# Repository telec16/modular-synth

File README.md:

# Telec's Modular Synth

~~Little side project, don't expect much updates.~~

# List of stuff I want to make

| 0%   | 10% | 20%       | 50%    | 65%     | 70%           | 75%  | 80%   | 100% |
|----- |---- |---------- |------- |-------- |-------------- |----- |------ |----- |
| Idea | POC | Schematic | Layout | Artwork | Final checkup | Prod | Tests | Done |

## Modules

* VCO
	- 3340
	- Schmitt inverter
	- Opamp V1 
	- Opamp V2 
* LFO
	- Hex Inverter
* Sequencer
	- µC
	- random jazz generator 
* Random generator
	- zener
	- µC
* ADSR
	- Opamp 
* VCA
	- LM13700 
	- Vactrol
* Quantizer (CV correction)
	- µC 
* VCF
	- ?
* Drum kit
	- ???
* Frequency multiplier/divider
	- CD4046 PLL V1 
	- CD4046 PLL V2 
* Wavefolder
	- Bipolar 
	- Opamp 
* CV Glider
	- RC circuit 
* Scope
	- µC 

## Instruments

* MiniSynth 
* MIDI I/O + CV Out keypad 

# Releases

* ADSR
* CV Glider
* VCA
* Wavefolder
* VCO
* PLL

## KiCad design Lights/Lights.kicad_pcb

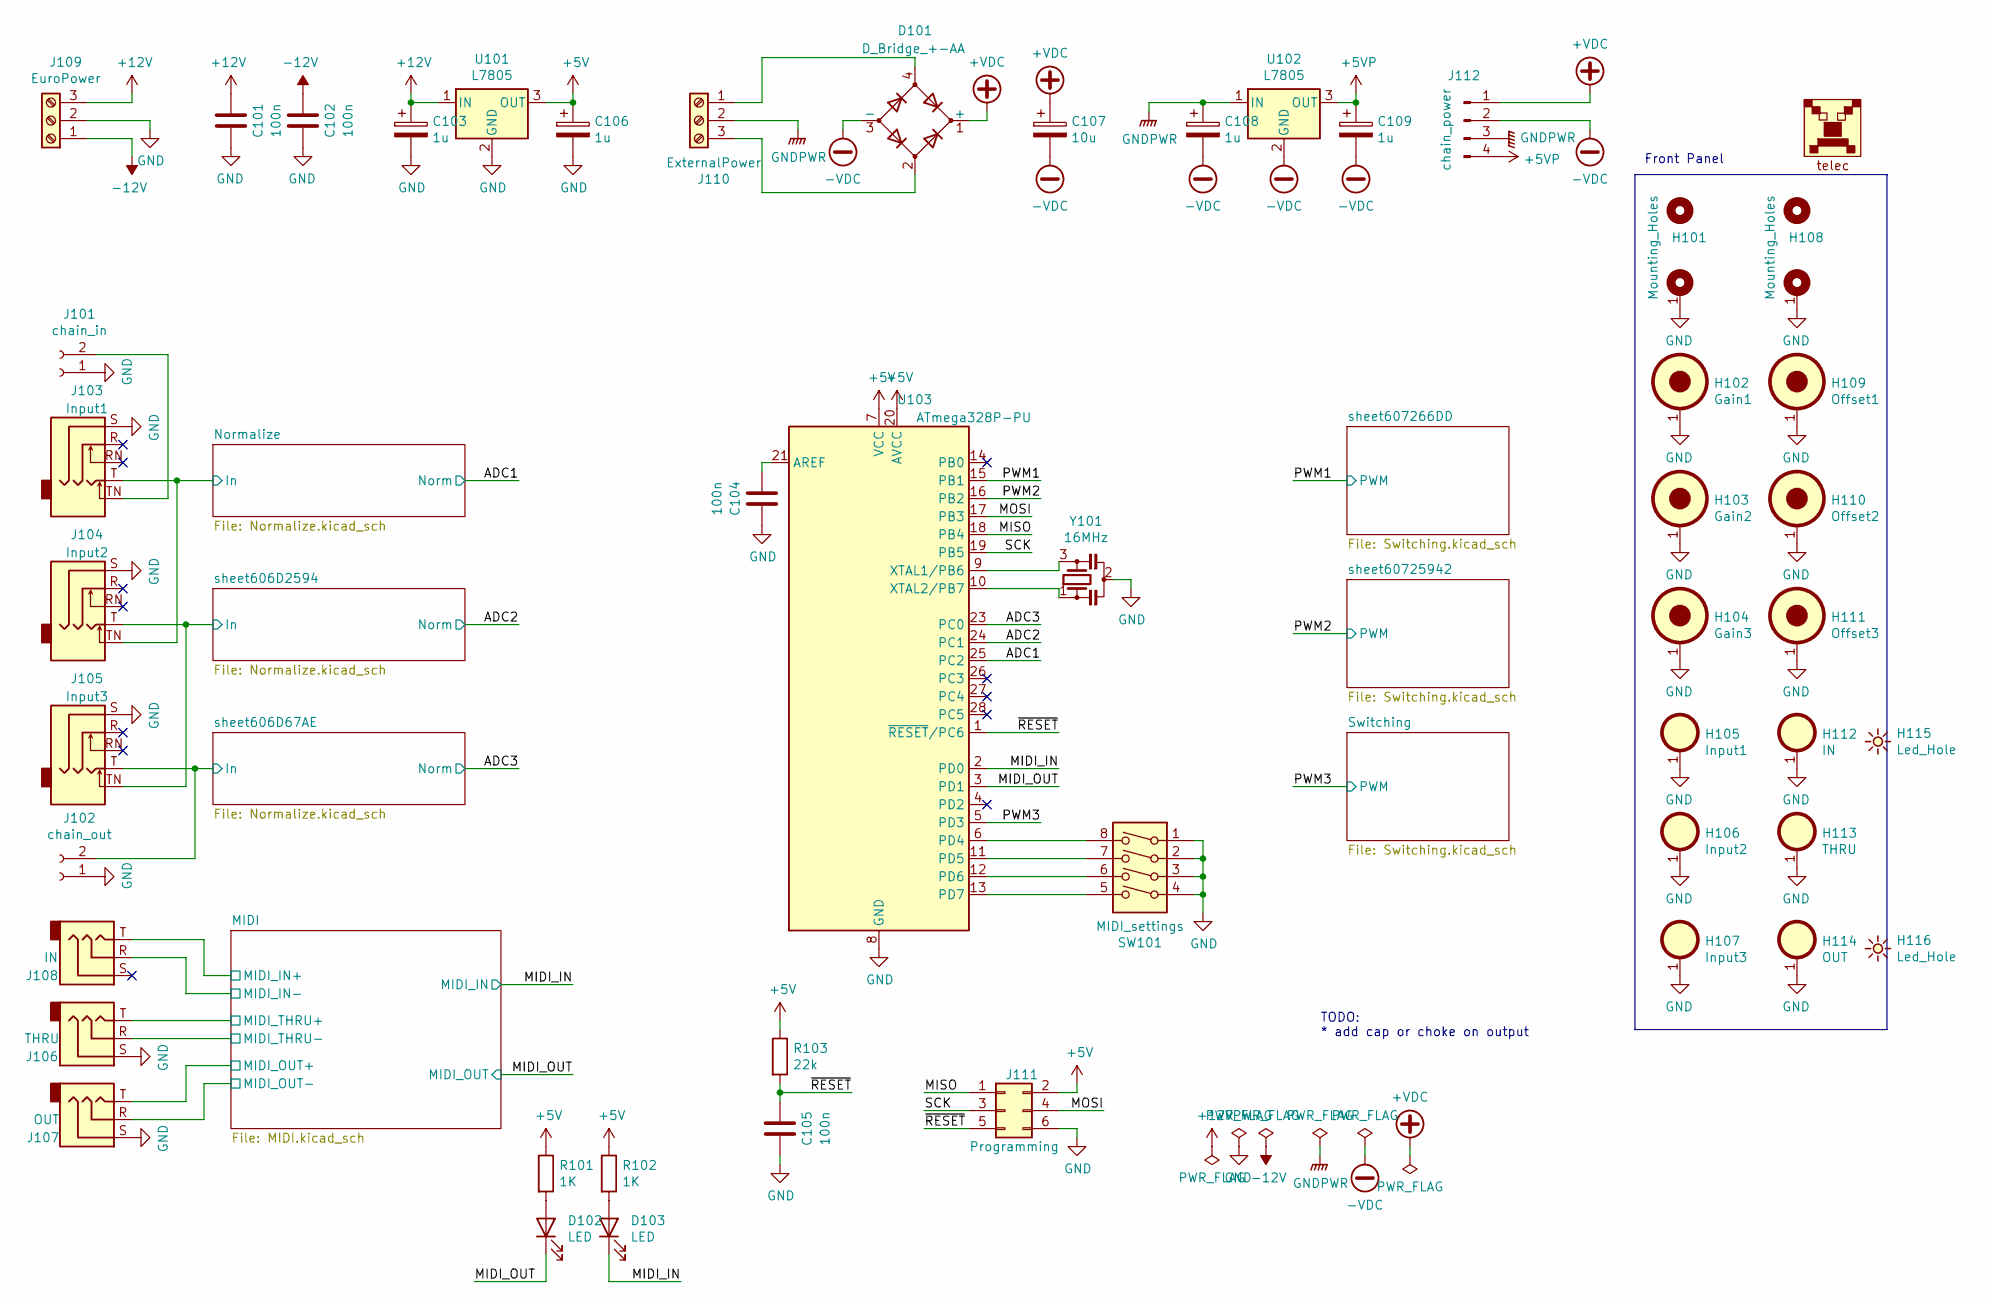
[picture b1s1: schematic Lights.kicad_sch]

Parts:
C101, C102, C104, C105: 100n; C_Disc_D7.0mm_W2.5mm_P5.00mm
C103, C106, C108, C109: 1u; CP_Radial_D5.0mm_P2.50mm
C107: 10u; CP_Radial_D5.0mm_P2.50mm
D101: D_Bridge_+-AA; Diode_Bridge_Round_D8.9mm
D102, D103: LED; LED_D3.0mm_FlatTop
H101, H108: Mounting_Holes; Kosmo_Panel_Dual_Mounting_Holes
H102: Gain1; Kosmo_Pot_Hole
H103: Gain2; Kosmo_Pot_Hole
H104: Gain3; Kosmo_Pot_Hole
H105: Input1; Kosmo_Jack_Hole
H106: Input2; Kosmo_Jack_Hole
H107: Input3; Kosmo_Jack_Hole
H109: Offset1; Kosmo_Pot_Hole
H110: Offset2; Kosmo_Pot_Hole
H111: Offset3; Kosmo_Pot_Hole
H112: IN; Kosmo_Jack_Hole
H113: THRU; Kosmo_Jack_Hole
H114: OUT; Kosmo_Jack_Hole
H115, H116: Led_Hole; Kosmo_LED_Hole
J101: chain_in; PinHeader_1x02_P2.54mm_Vertical
J102: chain_out; PinHeader_1x02_P2.54mm_Vertical
J103: Input1; Jack_6.35mm_PJ_629HAN
J104: Input2; Jack_6.35mm_PJ_629HAN
J105: Input3; Jack_6.35mm_PJ_629HAN
J106: THRU; PinHeader_TRS_P2.54mm_Vertical
J107: OUT; PinHeader_TRS_P2.54mm_Vertical
J108: IN; PinHeader_TRS_P2.54mm_Vertical
J109: EuroPower
J110: ExternalPower; TerminalBlock_bornier-3_P5.08mm
J111: Programming; IDC-Header_2x03_P2.54mm_Vertical
J112: chain_power; PinHeader_1x04_P2.54mm_Vertical
LOGO101: telec; telec-8
R101, R102: 1K; R_Axial_DIN0204_L3.6mm_D1.6mm_P2.54mm_Vertical
R103: 22k; R_Axial_DIN0204_L3.6mm_D1.6mm_P2.54mm_Vertical
SW101: MIDI_settings; SW_DIP_SPSTx04_Slide_9.78x12.34mm_W7.62mm_P2.54mm
U101, U102: L7805; TO-220-3_Vertical
U103: ATmega328P-PU; DIP-28_W7.62mm
Y101: 16MHz; Resonator-3Pin_W6.0mm_H3.0mm

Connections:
+5V: C106.1, J111.2, R101.1, R102.1, R103.1, U101.3 (OUT), U103.7 (VCC), U103.20 (AVCC); also elsewhere on the board
+5VP: C109.1, J112.4, U102.3 (OUT); also elsewhere on the board
+12V: C101.2, C103.1, J109.3, U101.1 (IN); also elsewhere on the board
+VDC: C107.1, D101.1 (+), J112.1; also elsewhere on the board
-12V: C102.2, J109.1; also elsewhere on the board
-VDC: C107.2, C108.2, C109.2, D101.3 (-), J112.2, U102.2 (GND); also elsewhere on the board
/ADC1: U103.25 (PC2); also elsewhere on the board
/ADC2: U103.24 (PC1); also elsewhere on the board
/ADC3: U103.23 (PC0); also elsewhere on the board
/MIDI/MIDI_IN+: J108.T; also elsewhere on the board
/MIDI/MIDI_IN-: J108.R; also elsewhere on the board
/MIDI/MIDI_OUT+: J107.T; also elsewhere on the board
/MIDI/MIDI_OUT-: J107.R; also elsewhere on the board
/MIDI/MIDI_THRU+: J106.T; also elsewhere on the board
/MIDI/MIDI_THRU-: J106.R; also elsewhere on the board
/MIDI_IN: D103.1 (K), U103.2 (PD0); also elsewhere on the board
/MIDI_OUT: D102.1 (K), U103.3 (PD1); also elsewhere on the board
/MISO: J111.1, U103.18 (PB4)
/MOSI: J111.4, U103.17 (PB3)
/Normalize/In: J103.T, J104.TN; also elsewhere on the board
/PWM1: U103.15 (PB1); also elsewhere on the board
/PWM2: U103.16 (PB2); also elsewhere on the board
/PWM3: U103.5 (PD3); also elsewhere on the board
/SCK: J111.3, U103.19 (PB5)
/sheet606D67AE/In: J102.2, J105.T; also elsewhere on the board
/sheet606D2594/In: J104.T, J105.TN; also elsewhere on the board
/~RESET: C105.2, J111.5, R103.2, U103.1 (~RESET/PC6)
GND: C101.1, C102.1, C103.2, C104.1, C105.1, C106.2, H101.1, H102.1, H103.1, H104.1, H105.1, H106.1, H107.1, H108.1, H109.1, H110.1, H111.1, H112.1, H113.1, H114.1, J101.1, J102.1, J103.S, J104.S, J105.S, J106.S, J107.S, J109.2, J111.6, SW101.1, SW101.2, SW101.3, SW101.4, U101.2 (GND), U103.8 (GND), U103.22 (GND), Y101.2; also elsewhere on the board
GNDPWR: C108.1, J110.2, J112.3, U102.1 (IN)
unnamed: D102.2 (A), R101.2
unnamed: D103.2 (A), R102.2
unnamed: J101.2, J103.TN
unnamed: D101.4, J110.1
unnamed: D101.2, J110.3
unnamed: C104.2, U103.21 (AREF)
unnamed: SW101.8, U103.6 (PD4)
unnamed: SW101.7, U103.11 (PD5)
unnamed: SW101.6, U103.12 (PD6)
unnamed: SW101.5, U103.13 (PD7)
unnamed: U103.9 (XTAL1/PB6), Y101.3
unnamed: U103.10 (XTAL2/PB7), Y101.1

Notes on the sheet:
TODO: * add cap or choke on output
Front Panel

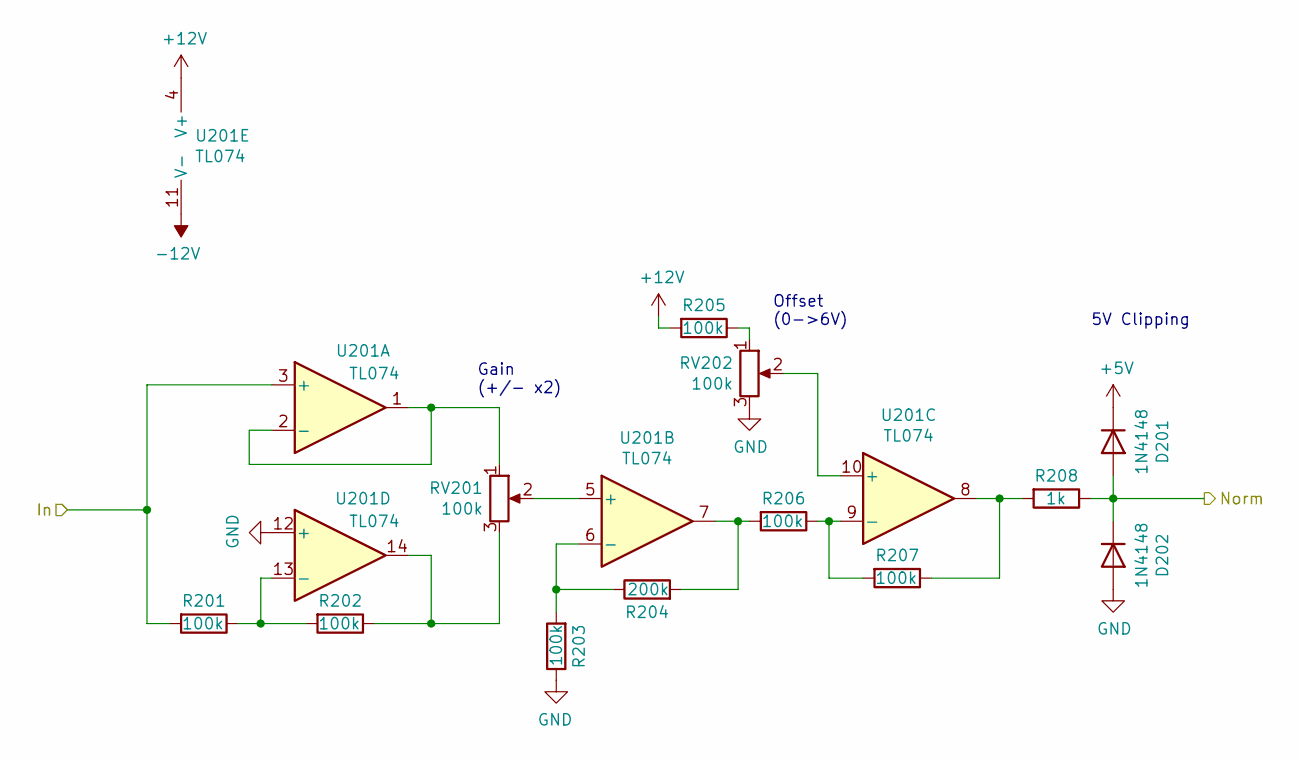
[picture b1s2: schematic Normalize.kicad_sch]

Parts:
D201, D202: 1N4148; D_DO-35_SOD27_P2.54mm_Vertical_KathodeUp
R201, R202, R203, R205, R207: 100k; R_Axial_DIN0204_L3.6mm_D1.6mm_P2.54mm_Vertical
R204: 200k; R_Axial_DIN0204_L3.6mm_D1.6mm_P2.54mm_Vertical
R206: 100k; R_Axial_DIN0204_L3.6mm_D1.6mm_P7.62mm_Horizontal
R208: 1k; R_Axial_DIN0204_L3.6mm_D1.6mm_P2.54mm_Vertical
RV201, RV202: 100k; PinHeader_1x03_P2.54mm_Vertical
U201: TL074; DIP-14_W7.62mm_LongPads

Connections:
+5V: D201.1 (K); also elsewhere on the board
+12V: R205.2, U201.4 (V+); also elsewhere on the board
-12V: U201.11 (V-); also elsewhere on the board
/ADC1: D201.2 (A), D202.1 (K), R208.1; also elsewhere on the board
/Normalize/In: R201.2, U201.3 (+); also elsewhere on the board
GND: D202.2 (A), R203.1, RV202.3, U201.12 (+); also elsewhere on the board
unnamed: R202.1, RV201.3, U201.14
unnamed: R204.2, R206.2, U201.7
unnamed: R205.1, RV202.1
unnamed: R207.1, R208.2, U201.8
unnamed: RV201.1, U201.1, U201.2 (-)
unnamed: RV201.2, U201.5 (+)
unnamed: R203.2, R204.1, U201.6 (-)
unnamed: RV202.2, U201.10 (+)
unnamed: R206.1, R207.2, U201.9 (-)
unnamed: R201.1, R202.2, U201.13 (-)

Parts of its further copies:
D501, D502, D601, D602: 1N4148; D_DO-35_SOD27_P2.54mm_Vertical_KathodeUp
R501, R502, R503, R505, R507, R601, R602, R603, R605, R607: 100k; R_Axial_DIN0204_L3.6mm_D1.6mm_P2.54mm_Vertical
R504, R604: 200k; R_Axial_DIN0204_L3.6mm_D1.6mm_P2.54mm_Vertical
R506, R606: 100k; R_Axial_DIN0204_L3.6mm_D1.6mm_P7.62mm_Horizontal
R508, R608: 1k; R_Axial_DIN0204_L3.6mm_D1.6mm_P2.54mm_Vertical
RV501, RV502, RV601, RV602: 100k; PinHeader_1x03_P2.54mm_Vertical
U501, U601: TL074; DIP-14_W7.62mm_LongPads

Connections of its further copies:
+5V: D501.1 (K), D601.1 (K); also elsewhere on the board
+12V: R505.2, R605.2, U501.4 (V+), U601.4 (V+); also elsewhere on the board
-12V: U501.11 (V-), U601.11 (V-); also elsewhere on the board
/ADC2: D501.2 (A), D502.1 (K), R508.1; also elsewhere on the board
/ADC3: D601.2 (A), D602.1 (K), R608.1; also elsewhere on the board
/sheet606D67AE/In: R601.2, U601.3 (+); also elsewhere on the board
/sheet606D2594/In: R501.2, U501.3 (+); also elsewhere on the board
GND: D502.2 (A), D602.2 (A), R503.1, R603.1, RV502.3, RV602.3, U501.12 (+), U601.12 (+); also elsewhere on the board
unnamed: R502.1, RV501.3, U501.14
unnamed: R504.2, R506.2, U501.7
unnamed: R505.1, RV502.1
unnamed: R507.1, R508.2, U501.8
unnamed: R602.1, RV601.3, U601.14
unnamed: R604.2, R606.2, U601.7
unnamed: R605.1, RV602.1
unnamed: R607.1, R608.2, U601.8
unnamed: RV501.1, U501.1, U501.2 (-)
unnamed: RV501.2, U501.5 (+)
unnamed: R503.2, R504.1, U501.6 (-)
unnamed: RV502.2, U501.10 (+)
unnamed: R506.1, R507.2, U501.9 (-)
unnamed: R501.1, R502.2, U501.13 (-)
unnamed: RV601.1, U601.1, U601.2 (-)
unnamed: RV601.2, U601.5 (+)
unnamed: R603.2, R604.1, U601.6 (-)
unnamed: RV602.2, U601.10 (+)
unnamed: R606.1, R607.2, U601.9 (-)
unnamed: R601.1, R602.2, U601.13 (-)

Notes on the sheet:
Offset (0->6V)
5V Clipping
Gain (+/- x2)

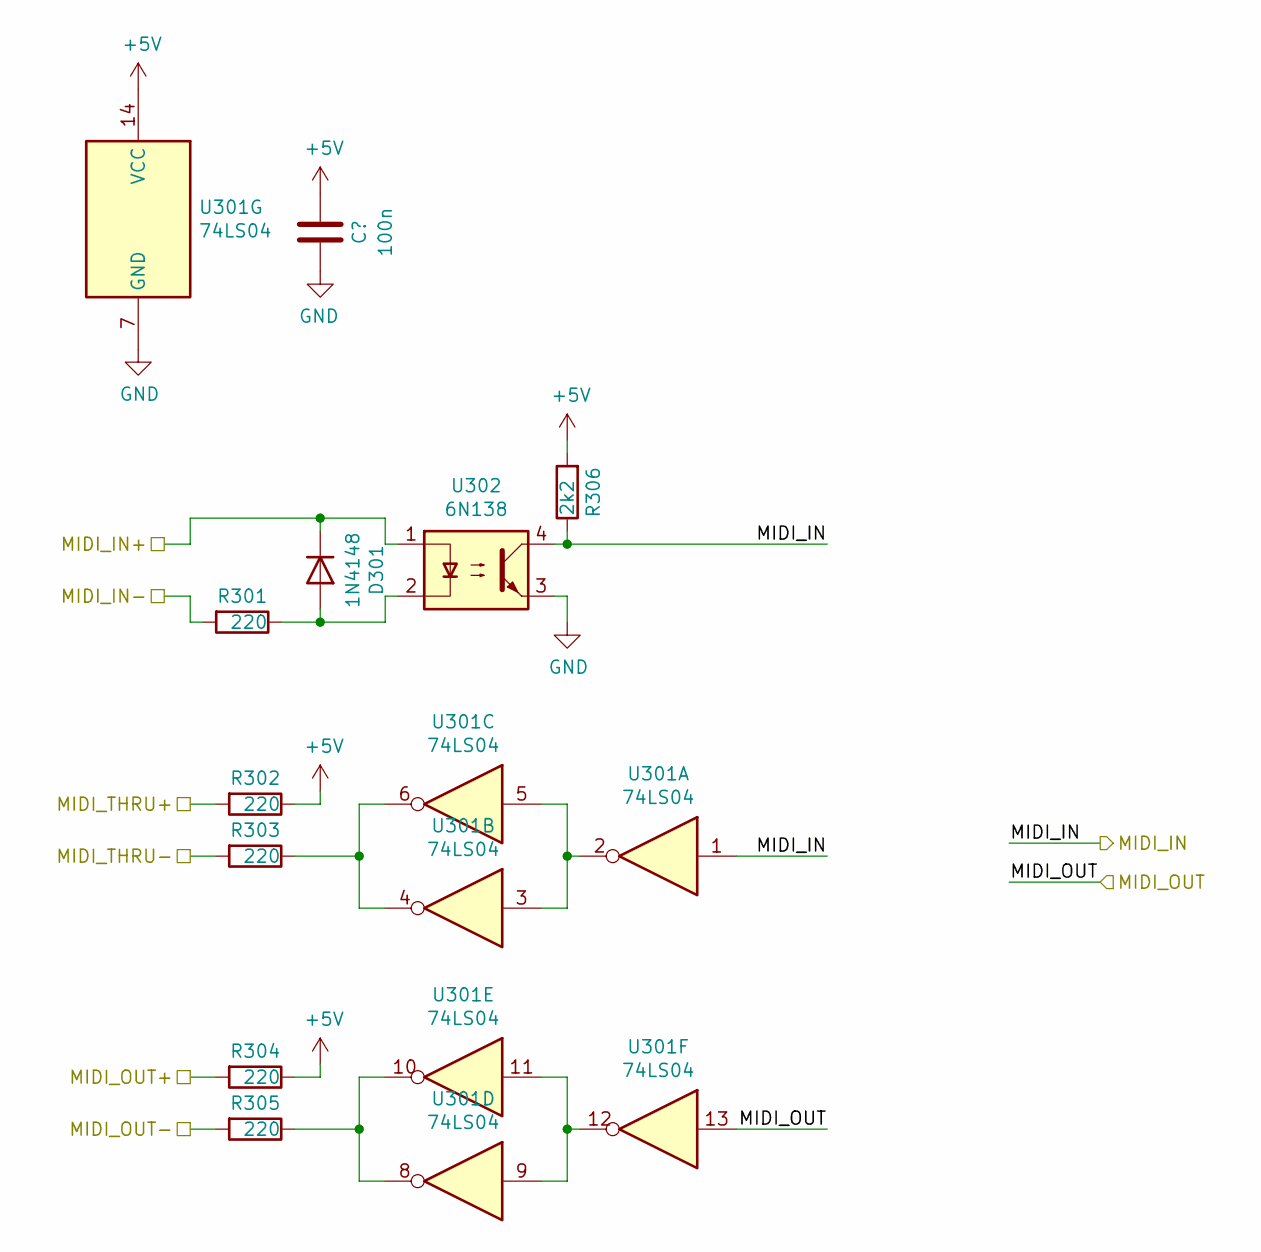
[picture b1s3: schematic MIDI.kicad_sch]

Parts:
C301: 100n; C_Disc_D7.0mm_W2.5mm_P5.00mm
D301: 1N4148; D_DO-35_SOD27_P2.54mm_Vertical_KathodeUp
R301, R302, R303, R304, R305: 220; R_Axial_DIN0204_L3.6mm_D1.6mm_P2.54mm_Vertical
R306: 2k2; R_Axial_DIN0204_L3.6mm_D1.6mm_P2.54mm_Vertical
U301: 74LS04; DIP-14_W7.62mm_LongPads
U302: 6N138; DIP-4_W7.62mm

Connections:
+5V: C301.2, R302.1, R304.1, R306.2, U301.14 (VCC); also elsewhere on the board
/MIDI/MIDI_IN+: D301.1 (K), U302.1; also elsewhere on the board
/MIDI/MIDI_IN-: R301.2; also elsewhere on the board
/MIDI/MIDI_OUT+: R304.2; also elsewhere on the board
/MIDI/MIDI_OUT-: R305.2; also elsewhere on the board
/MIDI/MIDI_THRU+: R302.2; also elsewhere on the board
/MIDI/MIDI_THRU-: R303.2; also elsewhere on the board
/MIDI_IN: R306.1, U301.1, U302.4; also elsewhere on the board
/MIDI_OUT: U301.13; also elsewhere on the board
GND: C301.1, U301.7 (GND), U302.3; also elsewhere on the board
unnamed: D301.2 (A), R301.1, U302.2
unnamed: R303.1, U301.4, U301.6
unnamed: R305.1, U301.8, U301.10
unnamed: U301.2, U301.3, U301.5
unnamed: U301.9, U301.11, U301.12

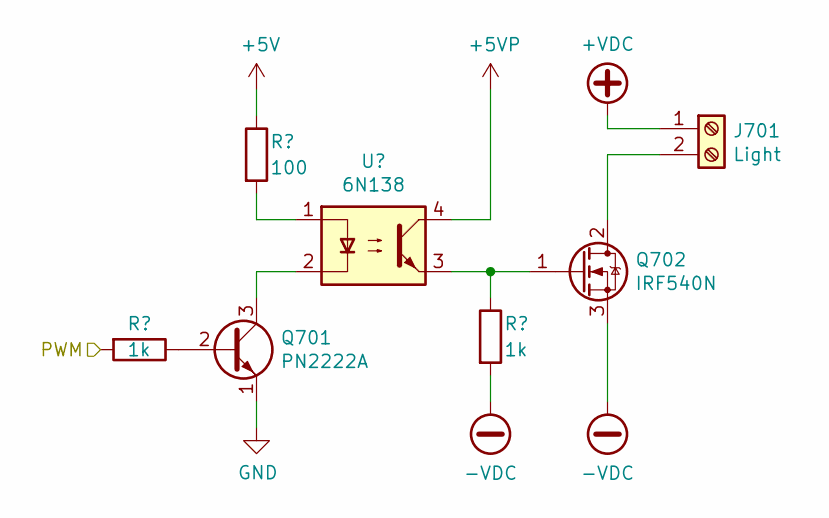
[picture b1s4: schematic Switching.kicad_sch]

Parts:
J701: Light; TerminalBlock_bornier-2_P5.08mm
Q701: PN2222A; TO-92_Inline_Wide
Q702: IRF540N; TO-220-3_Vertical
R701, R703: 1k; R_Axial_DIN0204_L3.6mm_D1.6mm_P2.54mm_Vertical
R702: 100; R_Axial_DIN0204_L3.6mm_D1.6mm_P2.54mm_Vertical
U701: 6N138; DIP-4_W7.62mm

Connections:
+5V: R702.1; also elsewhere on the board
+5VP: U701.4; also elsewhere on the board
+VDC: J701.1; also elsewhere on the board
-VDC: Q702.3 (S), R703.2; also elsewhere on the board
/PWM2: R701.2; also elsewhere on the board
GND: Q701.1 (E); also elsewhere on the board
unnamed: J701.2, Q702.2 (D)
unnamed: Q701.2 (B), R701.1
unnamed: Q701.3 (C), U701.2
unnamed: Q702.1 (G), R703.1, U701.3
unnamed: R702.2, U701.1

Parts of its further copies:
J401, J801: Light; TerminalBlock_bornier-2_P5.08mm
Q401, Q801: PN2222A; TO-92_Inline_Wide
Q402, Q802: IRF540N; TO-220-3_Vertical
R401, R403, R801, R803: 1k; R_Axial_DIN0204_L3.6mm_D1.6mm_P2.54mm_Vertical
R402, R802: 100; R_Axial_DIN0204_L3.6mm_D1.6mm_P2.54mm_Vertical
U401, U801: 6N138; DIP-4_W7.62mm

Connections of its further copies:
+5V: R402.1, R802.1; also elsewhere on the board
+5VP: U401.4, U801.4; also elsewhere on the board
+VDC: J401.1, J801.1; also elsewhere on the board
-VDC: Q402.3 (S), Q802.3 (S), R403.2, R803.2; also elsewhere on the board
/PWM1: R801.2; also elsewhere on the board
/PWM3: R401.2; also elsewhere on the board
GND: Q401.1 (E), Q801.1 (E); also elsewhere on the board
unnamed: J401.2, Q402.2 (D)
unnamed: J801.2, Q802.2 (D)
unnamed: Q401.2 (B), R401.1
unnamed: Q401.3 (C), U401.2
unnamed: Q402.1 (G), R403.1, U401.3
unnamed: Q801.2 (B), R801.1
unnamed: Q801.3 (C), U801.2
unnamed: Q802.1 (G), R803.1, U801.3
unnamed: R402.2, U401.1
unnamed: R802.2, U801.1

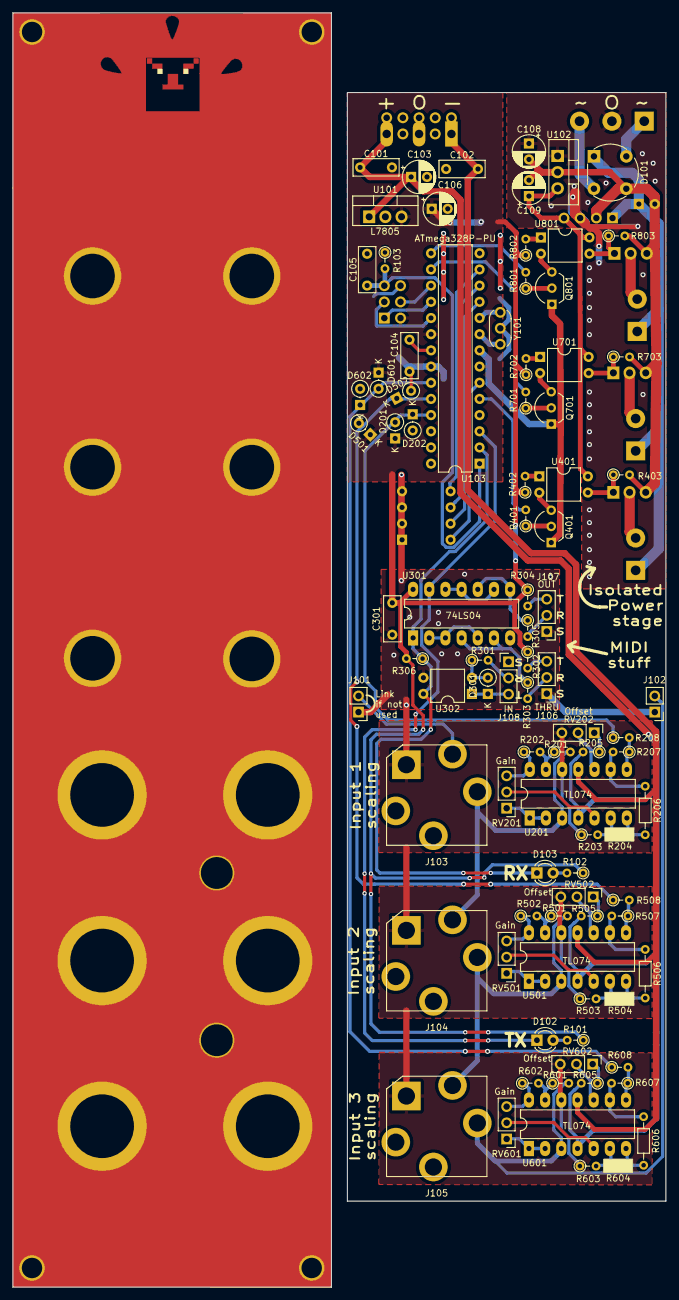
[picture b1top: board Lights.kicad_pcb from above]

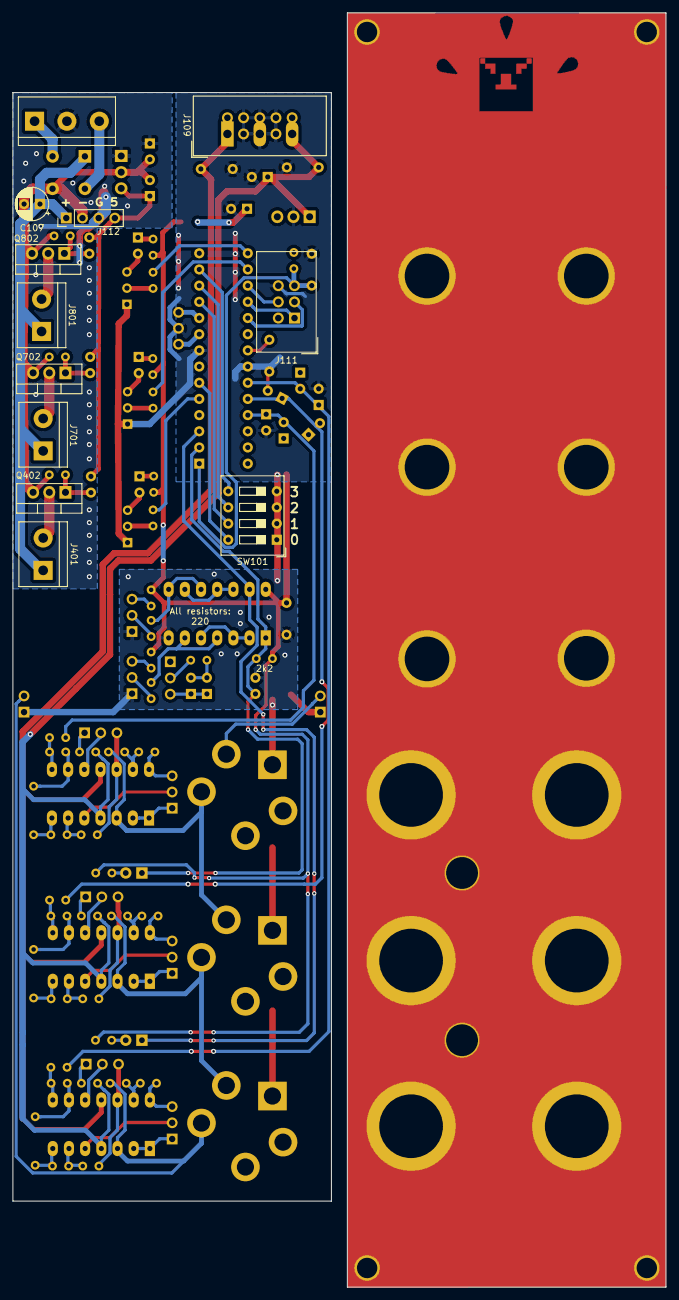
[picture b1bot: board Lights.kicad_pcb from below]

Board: 2 copper layers, 102.5 x 200.0 mm, 119 parts (12 on the bottom side), 91 nets.

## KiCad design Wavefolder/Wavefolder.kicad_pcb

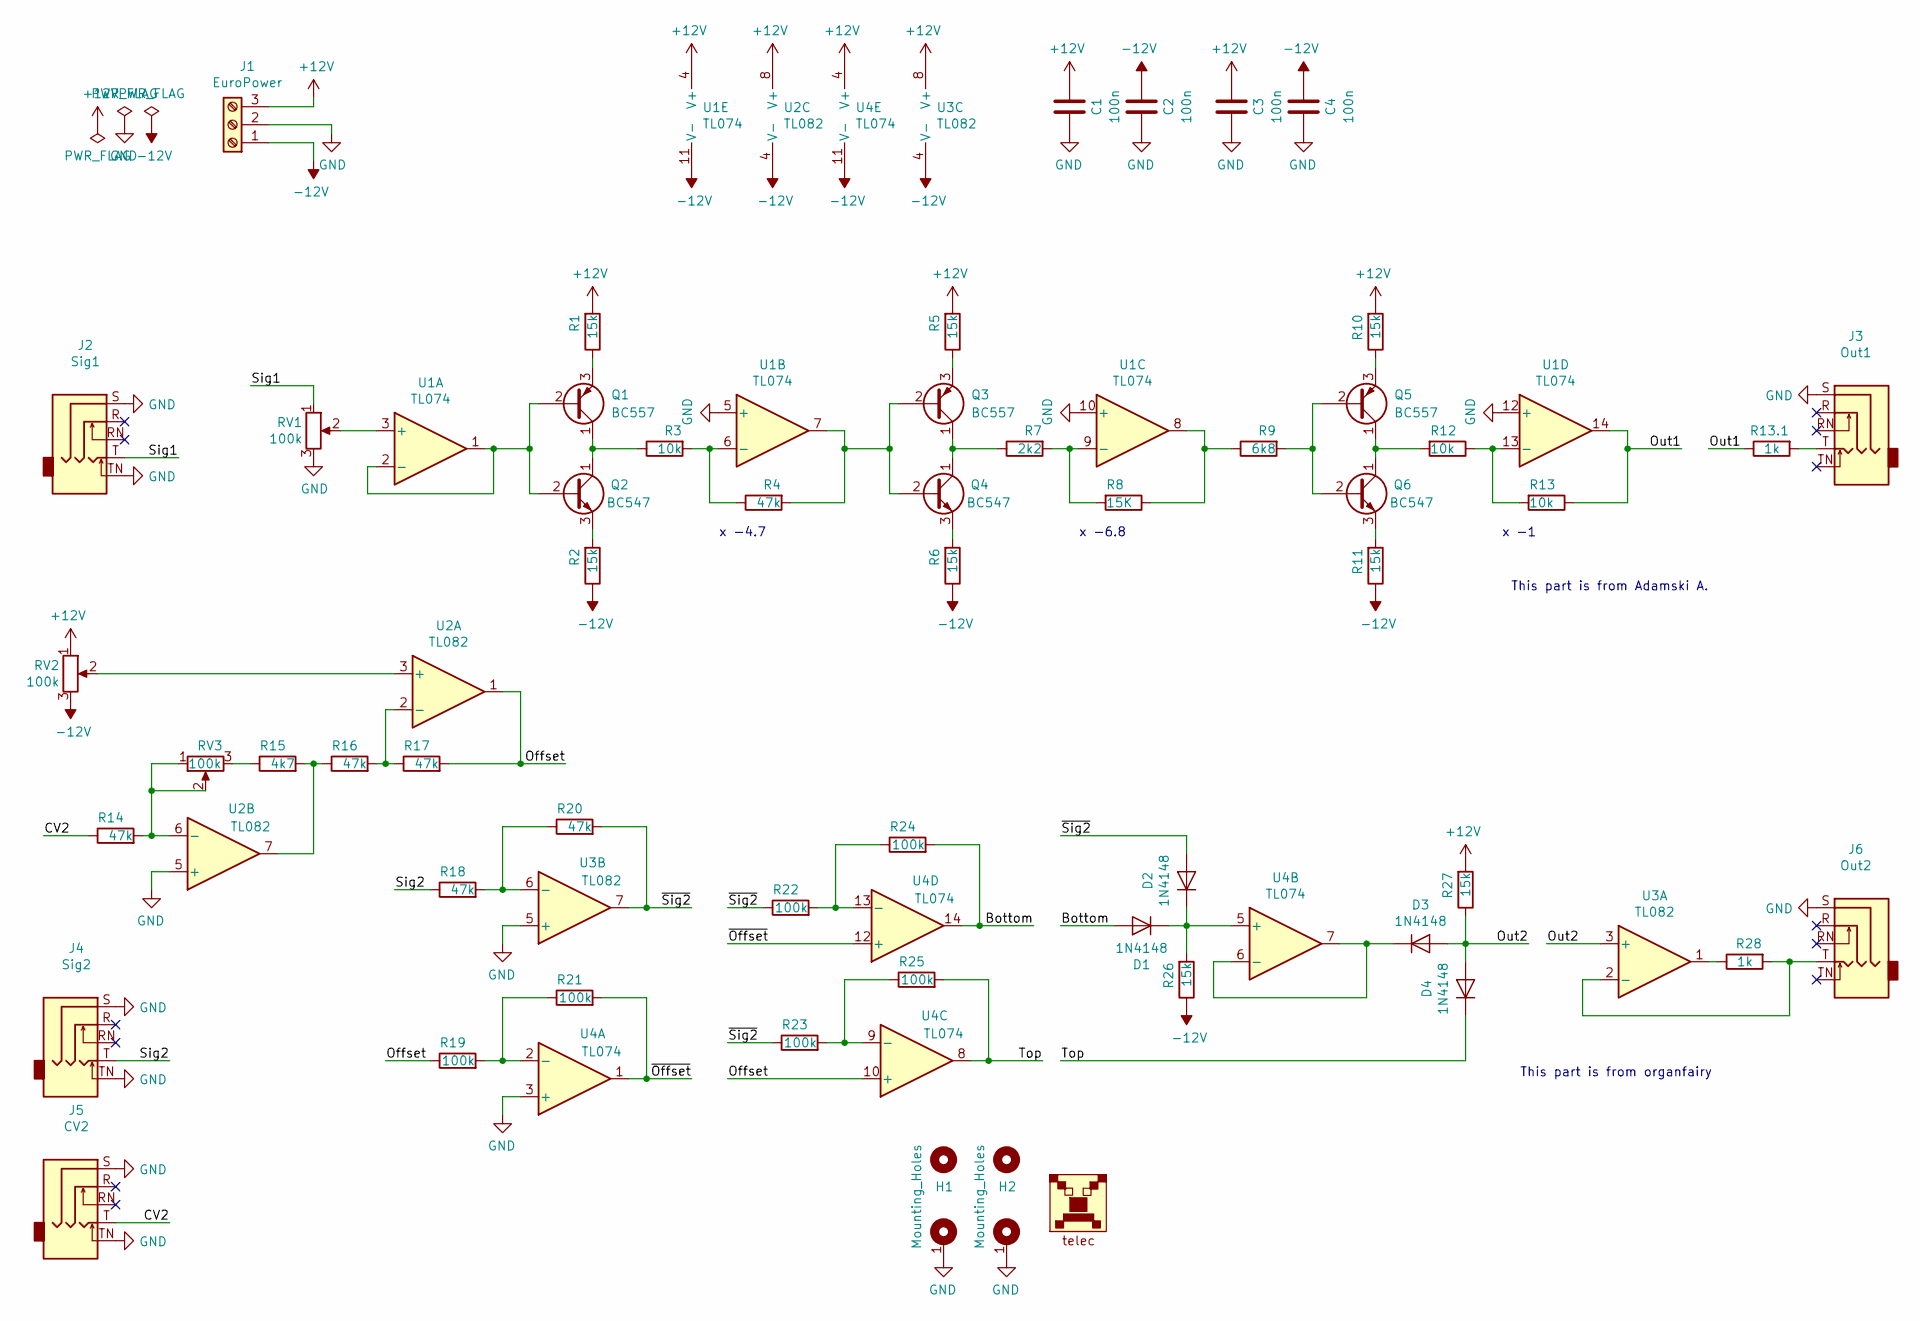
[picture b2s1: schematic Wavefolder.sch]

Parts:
C1, C2, C3, C4: 100n; C_1206_3216Metric
D1, D2, D3, D4: 1N4148; D_DO-35_SOD27_P7.62mm_Horizontal
H1, H2: Mounting_Holes; Kosmo_Panel_Dual_Mounting_Holes
J1: EuroPower
J2: Sig1; Jack_Hole_Square
J3: Out1; Jack_Hole_Square
J4: Sig2; Jack_Hole_Square
J5: CV2; Jack_Hole_Square
J6: Out2; Jack_Hole_Square
LOGO1: telec; telec-8
Q1, Q3, Q5: BC557; TO-92_Inline_Wide
Q2, Q4, Q6: BC547; TO-92_Inline_Wide
R1, R2, R5, R6, R10, R11: 15k; R_Axial_DIN0204_L3.6mm_D1.6mm_P2.54mm_Vertical
R3: 10k; R_Axial_DIN0204_L3.6mm_D1.6mm_P7.62mm_Horizontal
R4: 47k; R_Axial_DIN0204_L3.6mm_D1.6mm_P2.54mm_Vertical
R7: 2k2; R_Axial_DIN0204_L3.6mm_D1.6mm_P2.54mm_Vertical
R8: 15K; R_Axial_DIN0204_L3.6mm_D1.6mm_P2.54mm_Vertical
R9: 6k8; R_Axial_DIN0204_L3.6mm_D1.6mm_P2.54mm_Vertical
R12, R13: 10k; R_Axial_DIN0204_L3.6mm_D1.6mm_P2.54mm_Vertical
R13.1: 1k; R_Axial_DIN0204_L3.6mm_D1.6mm_P2.54mm_Vertical
R14, R16, R17, R18, R20: 47k; R_1206_3216Metric_Pad1.42x1.75mm_HandSolder
R15: 4k7; R_1206_3216Metric_Pad1.42x1.75mm_HandSolder
R19, R21, R22, R23, R25: 100k; R_Axial_DIN0204_L3.6mm_D1.6mm_P7.62mm_Horizontal
R24: 100k; R_Axial_DIN0204_L3.6mm_D1.6mm_P2.54mm_Vertical
R26, R27: 15k; R_Axial_DIN0204_L3.6mm_D1.6mm_P7.62mm_Horizontal
R28: 1k; R_1206_3216Metric_Pad1.42x1.75mm_HandSolder
RV1, RV2, RV3: 100k; Potentiometer_Alps_RK09K_Single_Vertical
U1, U4: TL074; DIP-14_W7.62mm_LongPads
U2, U3: TL082; SOIC-8_3.9x4.9mm_P1.27mm

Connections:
+12V: C1.2, C3.2, J1.3, R1.2, R5.2, R10.2, R27.2, RV2.1, U1.4 (V+), U2.8 (V+), U3.8 (V+), U4.4 (V+)
-12V: C2.2, C4.2, J1.1, R2.1, R6.1, R11.1, R26.1, RV2.3, U1.11 (V-), U2.4 (V-), U3.4 (V-), U4.11 (V-)
/Bottom: D1.2 (A), R24.2, U4.14
/CV2: J5.T, R14.1
/Offset: R17.2, R19.1, U2.1, U4.10 (+)
/Out1: R13.1, R13.1.1, U1.14
/Out2: D3.2 (A), D4.2 (A), R27.1, U3.3 (+)
/Sig1: J2.T, RV1.1
/Sig2: J4.T, R18.1
/Top: D4.1 (K), R25.2, U4.8
/~Offset: R21.2, U4.1, U4.12 (+)
/~Sig2: D2.2 (A), R20.2, R22.1, R23.1, U3.7
GND: C1.1, C2.1, C3.1, C4.1, H1.1, H2.1, J1.2, J2.S, J2.TN, J3.S, J4.S, J4.TN, J5.S, J5.TN, J6.S, RV1.3, U1.5 (+), U1.10 (+), U1.12 (+), U2.5 (+), U3.5 (+), U4.3 (+)
unnamed: D1.1 (K), D2.1 (K), R26.2, U4.5 (+)
unnamed: D3.1 (K), U4.6 (-), U4.7
unnamed: J3.T, R13.1.2
unnamed: J6.T, R28.2, U3.2 (-)
unnamed: Q1.1 (C), Q2.1 (C), R3.1
unnamed: Q1.2 (B), Q2.2 (B), U1.1, U1.2 (-)
unnamed: Q1.3 (E), R1.1
unnamed: Q2.3 (E), R2.2
unnamed: Q3.1 (C), Q4.1 (C), R7.1
unnamed: Q3.2 (B), Q4.2 (B), R4.2, U1.7
unnamed: Q3.3 (E), R5.1
unnamed: Q4.3 (E), R6.2
unnamed: Q5.1 (C), Q6.1 (C), R12.2
unnamed: Q5.2 (B), Q6.2 (B), R9.2
unnamed: Q5.3 (E), R10.1
unnamed: Q6.3 (E), R11.2
unnamed: R3.2, R4.1, U1.6 (-)
unnamed: R7.2, R8.2, U1.9 (-)
unnamed: R8.1, R9.1, U1.8
unnamed: R12.1, R13.2, U1.13 (-)
unnamed: R14.2, RV3.1, RV3.2, U2.6 (-)
unnamed: R15.1, RV3.3
unnamed: R15.2, R16.1, U2.7
unnamed: R16.2, R17.1, U2.2 (-)
unnamed: R18.2, R20.1, U3.6 (-)
unnamed: R19.2, R21.1, U4.2 (-)
unnamed: R22.2, R24.1, U4.13 (-)
unnamed: R23.2, R25.1, U4.9 (-)
unnamed: R28.1, U3.1
unnamed: RV1.2, U1.3 (+)
unnamed: RV2.2, U2.3 (+)

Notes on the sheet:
x -4.7
x -6.8
x -1
This part is from Adamski A.
This part is from organfairy

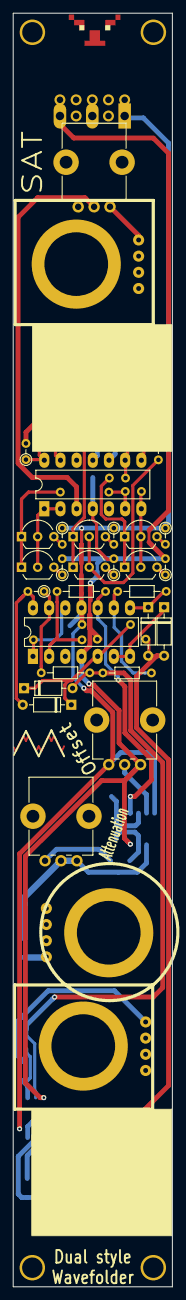
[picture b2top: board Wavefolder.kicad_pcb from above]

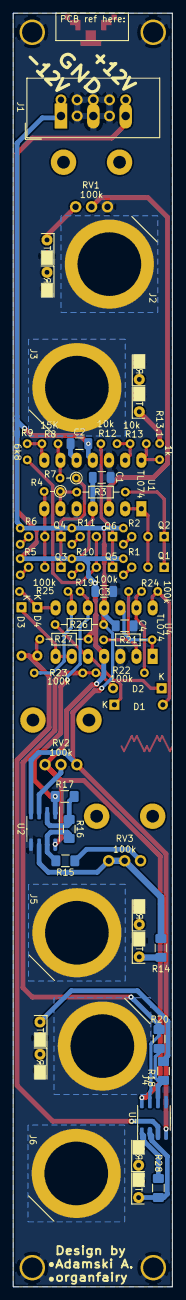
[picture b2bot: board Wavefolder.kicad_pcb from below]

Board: 2 copper layers, 25.0 x 200.0 mm, 59 parts (20 on the bottom side), 44 nets.

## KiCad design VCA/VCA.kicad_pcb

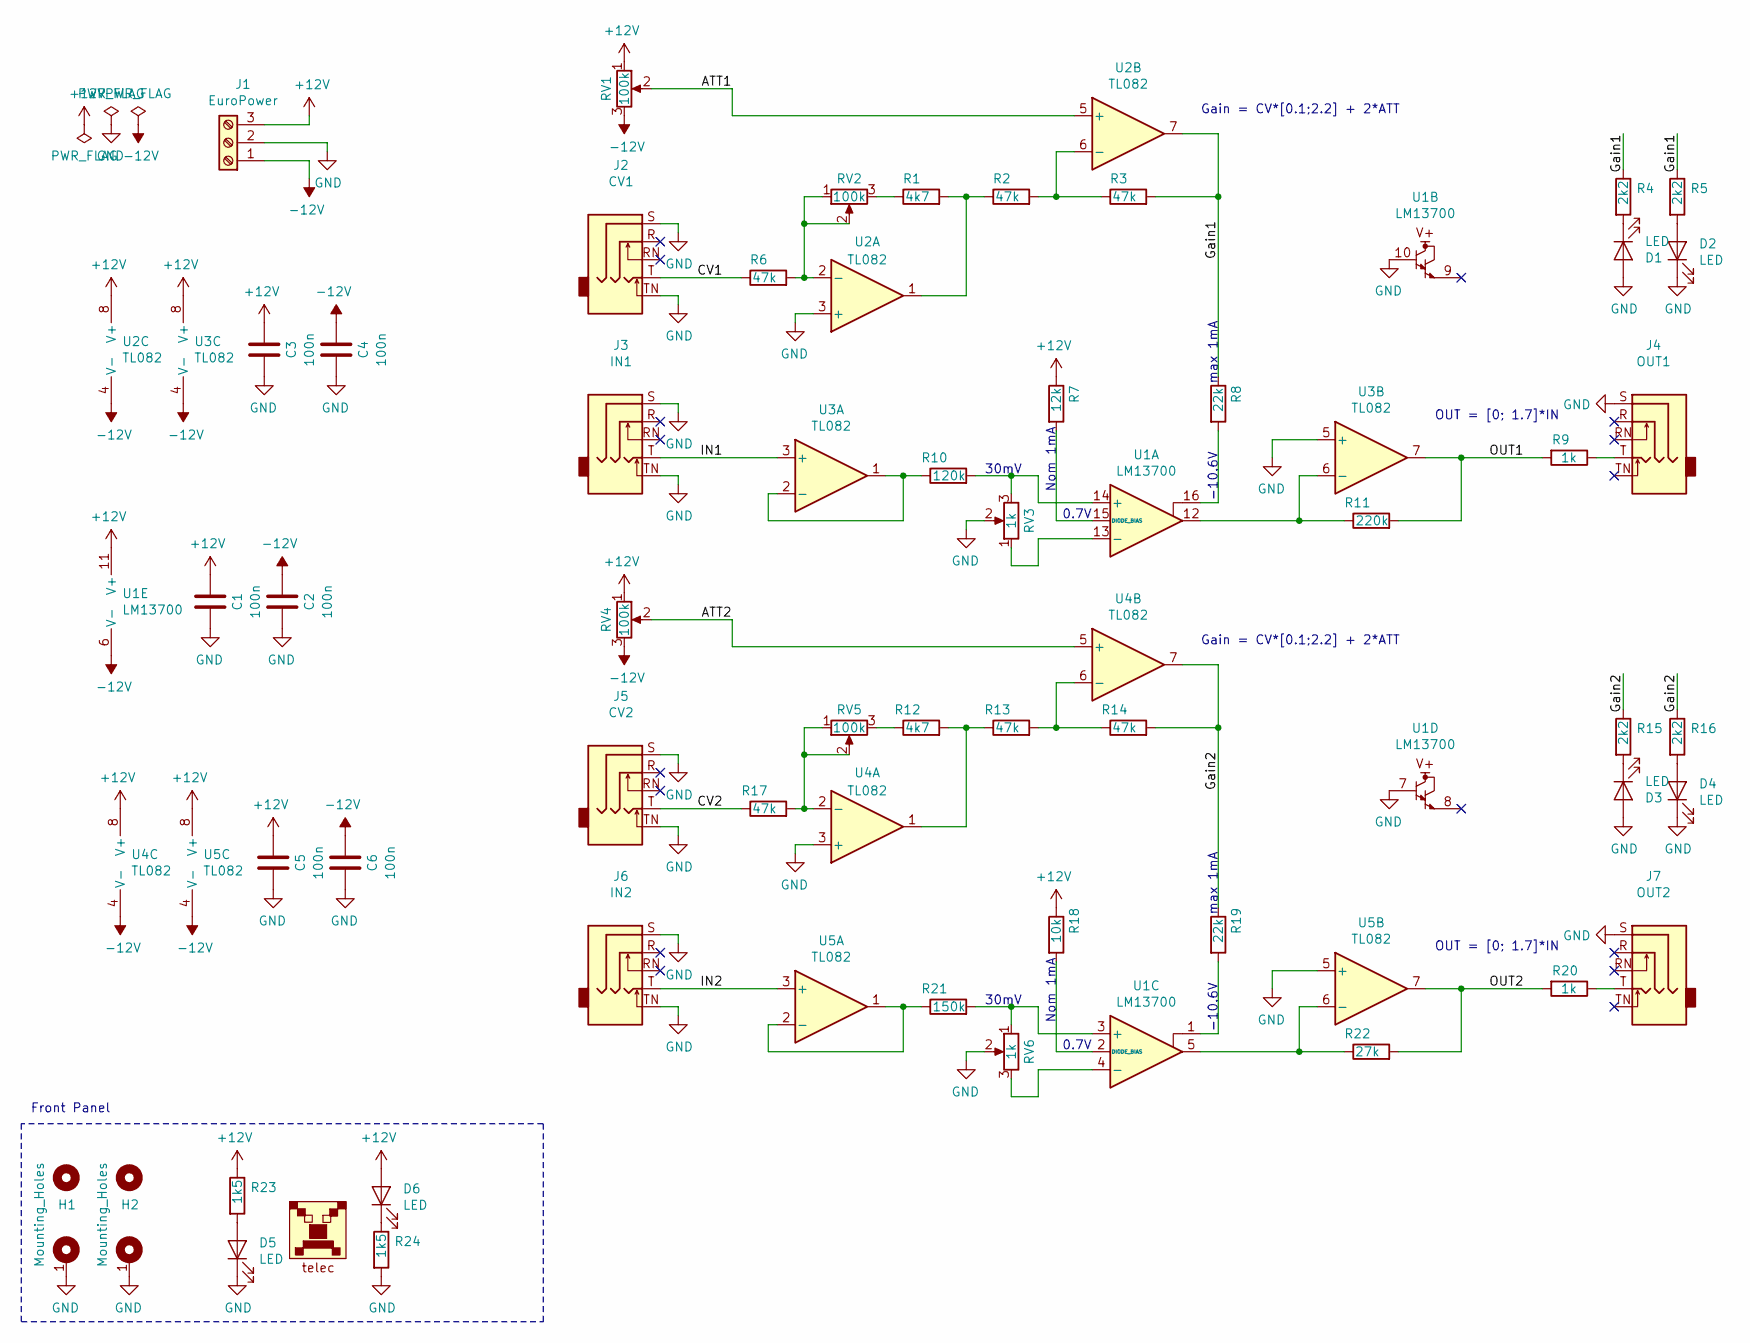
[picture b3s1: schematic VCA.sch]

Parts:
C1, C2, C3, C4, C5, C6: 100n; C_1206_3216Metric_Pad1.42x1.75mm_HandSolder
D1, D2, D3, D4: LED; LED_1206_3216Metric_ReverseMount_Hole1.8x2.4mm
D5, D6: LED; LED_1206_3216Metric_Castellated
H1, H2: Mounting_Holes; Kosmo_Panel_Dual_Mounting_Holes
J1: EuroPower
J2: CV1; Jack_Hole_Square
J3: IN1; Jack_Hole_Square
J4: OUT1; Jack_Hole_Square
J5: CV2; Jack_Hole_Square
J6: IN2; Jack_Hole_Square
J7: OUT2; Jack_Hole_Square
LOGO1: telec; telec-16
R1, R12: 4k7; R_1206_3216Metric_Pad1.42x1.75mm_HandSolder
R2, R3, R6, R13, R14, R17: 47k; R_1206_3216Metric_Pad1.42x1.75mm_HandSolder
R4, R5, R15, R16: 2k2; R_1206_3216Metric_Pad1.42x1.75mm_HandSolder
R7: 12k; R_1206_3216Metric_Pad1.42x1.75mm_HandSolder
R8, R19: 22k; R_1206_3216Metric_Pad1.42x1.75mm_HandSolder
R9, R20: 1k; R_1206_3216Metric_Pad1.42x1.75mm_HandSolder
R10: 120k; R_1206_3216Metric_Pad1.42x1.75mm_HandSolder
R11: 220k; R_1206_3216Metric_Pad1.42x1.75mm_HandSolder
R18: 10k; R_1206_3216Metric_Pad1.42x1.75mm_HandSolder
R21: 150k; R_1206_3216Metric_Pad1.42x1.75mm_HandSolder
R22: 27k; R_1206_3216Metric_Pad1.42x1.75mm_HandSolder
R23, R24: 1k5; R_1206_3216Metric_Pad1.42x1.75mm_HandSolder
RV1, RV2, RV4, RV5: 100k; Potentiometer_Single_Vertical_Hole
RV3, RV6: 1k; Potentiometer_P3.81mmx5.12mm_Vertical
U1: LM13700; SOIC-16_3.9x9.9mm_P1.27mm
U2, U3, U4, U5: TL082; SOIC-8_3.9x4.9mm_P1.27mm

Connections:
+12V: C1.2, C3.2, C5.2, D6.2 (A), J1.3, R7.1, R18.1, R23.1, RV1.1, RV4.1, U1.11 (V+), U2.8 (V+), U3.8 (V+), U4.8 (V+), U5.8 (V+)
-12V: C2.2, C4.2, C6.2, J1.1, RV1.3, RV4.3, U1.6 (V-), U2.4 (V-), U3.4 (V-), U4.4 (V-), U5.4 (V-)
/ATT1: RV1.2, U2.5 (+)
/ATT2: RV4.2, U4.5 (+)
/CV1: J2.T, R6.1
/CV2: J5.T, R17.1
/Gain1: R3.2, R4.1, R5.1, R8.1, U2.7
/Gain2: R14.2, R15.1, R16.1, R19.1, U4.7
/IN1: J3.T, U3.3 (+)
/IN2: J6.T, U5.3 (+)
/OUT1: R9.2, R11.2, U3.7
/OUT2: R20.2, R22.2, U5.7
GND: C1.1, C2.1, C3.1, C4.1, C5.1, C6.1, D1.2 (A), D2.1 (K), D3.2 (A), D4.1 (K), D5.1 (K), H1.1, H2.1, J1.2, J2.S, J2.TN, J3.S, J3.TN, J4.S, J5.S, J5.TN, J6.S, J6.TN, J7.S, R24.2, RV3.2, RV6.2, U1.7, U1.10, U2.3 (+), U3.5 (+), U4.3 (+), U5.5 (+)
unnamed: D1.1 (K), R4.2
unnamed: D2.2 (A), R5.2
unnamed: D3.1 (K), R15.2
unnamed: D4.2 (A), R16.2
unnamed: D5.2 (A), R23.2
unnamed: D6.1 (K), R24.1
unnamed: J4.T, R9.1
unnamed: J7.T, R20.1
unnamed: R1.1, RV2.3
unnamed: R1.2, R2.1, U2.1
unnamed: R2.2, R3.1, U2.6 (-)
unnamed: R6.2, RV2.1, RV2.2, U2.2 (-)
unnamed: R7.2, U1.15 (DIODE_BIAS)
unnamed: R8.2, U1.16
unnamed: R10.1, U3.1, U3.2 (-)
unnamed: R10.2, RV3.3, U1.14 (+)
unnamed: R11.1, U1.12, U3.6 (-)
unnamed: R12.1, RV5.3
unnamed: R12.2, R13.1, U4.1
unnamed: R13.2, R14.1, U4.6 (-)
unnamed: R17.2, RV5.1, RV5.2, U4.2 (-)
unnamed: R18.2, U1.2 (DIODE_BIAS)
unnamed: R19.2, U1.1
unnamed: R21.1, U5.1, U5.2 (-)
unnamed: R21.2, RV6.1, U1.3 (+)
unnamed: R22.1, U1.5, U5.6 (-)
unnamed: RV3.1, U1.13 (-)
unnamed: RV6.3, U1.4 (-)

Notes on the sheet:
Gain = CV*[0.1;2.2] + 2*ATT
-10.6V
max 1mA
Nom 1mA
0.7V
30mV
OUT = [0; 1.7]*IN
Front Panel
